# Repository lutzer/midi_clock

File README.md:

# Midi Clock

## Requirements

* install rust
  * run `curl --proto '=https' --tlsv1.2 -sSf https://sh.rustup.rs | sh` to install rust toolchain
  * use nightly toolchain: `rustup default nightly` (for heap allocator)
  * install target `rustup target install thumbv7m-none-eabi`
  * install cargo-edit `cargo install cargo-edit`, it allows to add dependencies with `cargo add <package>`

* install flash toolchain
  * install stlink on mac with `brew install stlink`
  * install *binutils-arm-none-eabi* with `brew tap PX4/homebrew-px4; brew install gcc-arm-none-eabi`

## Connect Board

* disconnect external power supply
* connect programmer *ST-Link V2* to programming pins of blue pill. Connect pins *SWDIO, GND, SWCLK, and 3.3V and RST to pin R*
* check if programmer is avalaible with `st-info --probe`

## Flash Chip

* run `./flash`
* compile with features with `./flash "feature1,feature2,..."`

## Debugging

* for debugging connect serial adapter, see in [docs/hardware.md](docs/hardware.md)
* flash chip with debug feature: `./flash debug`
* see debugging output with `screen /dev/tty.<adapter> 115200`, (Ctrl+A, K to close monitor)
* for analyzing the timings of the midi clock see [tools/clock_test/README.md](tools/clock_test/README.md)

## Links

* Midi specifications: https://www.midi.org/specifications-old/item/table-1-summary-of-midi-message
* STM32f103 Reference Manual: https://www.st.com//content/ccc/resource/technical/document/reference_manual/59/b9/ba/7f/11/af/43/d5/CD00171190.pdf/files/CD00171190.pdf/jcr:content/translations/en.CD00171190.pdf
* LCD 0802A: http://www.farnell.com/datasheets/50552.pdf
* Timer registers for stm32f103: https://docs.rs/stm32f1/0.14.0/stm32f1/stm32f103/tim2/index.html

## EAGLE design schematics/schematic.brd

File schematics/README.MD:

# Midi Clock Schematics

## Setup
* copy libraries from libraries folder to eagle libraries folder
* copy schematics to eagle project folder
* open project
* activate libraries with right click and use in library manager -> use library

## BOM

## PCB Specs

* drill whole sice 0.2mm - 6.3mm
* via size: hole: 0.2mm, copper ring: 0.4mm
* plated hole size: 0.2-6.35
* min clearences
  * hole to hole: 0.5mm
  * via to via: 0.254mm
  * pad to pad with hole: 0.5mm
  * pth to track: 0.33
  * pad to track: 0.2
  * trace width: minimum 0.2mm
  * spacing: 0.2mm

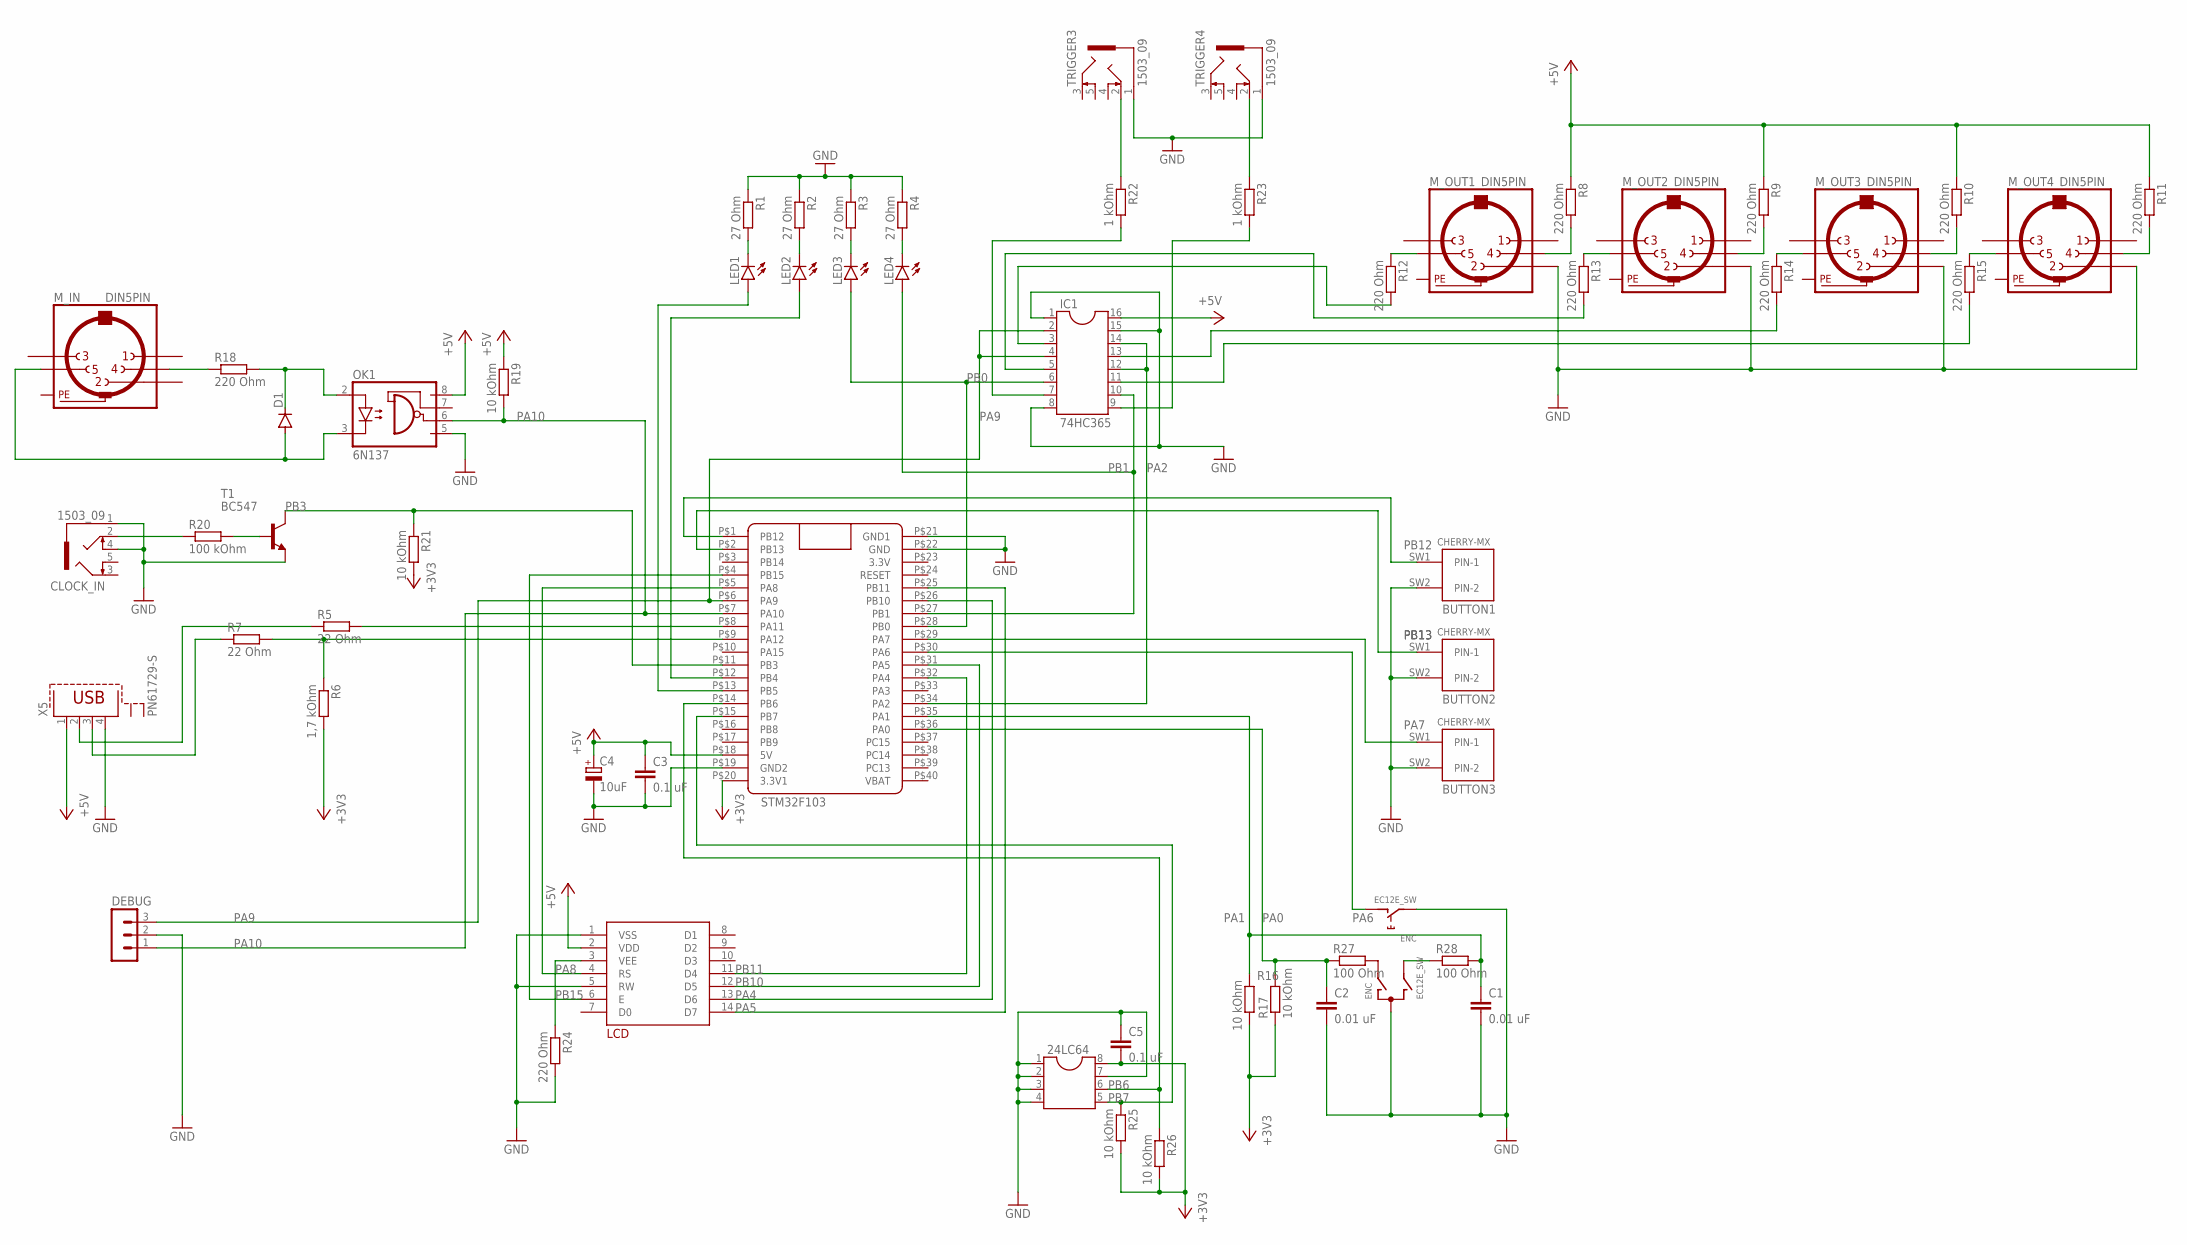
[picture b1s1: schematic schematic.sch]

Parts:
24LC64: DIL8; DIL08
BUTTON1, BUTTON2, BUTTON3: CHERRY-MX
C1, C2: 0.01 uF; C050-025X075
C3, C5: 0.1 uF; C050-025X075
C4: 10uF; E2,5-6
CLOCK_IN: 1503_09
D1: 1N4446; DO35-10
DEBUG: MA03-1
ENC: EC12E_SW; ALPS_EC12E_SW
IC1: 74HC365; SOCKET-16
LCD: LCD-MODUL2X8
LED1, LED2, LED3, LED4: LED3MM
M_IN: DIN5PIN; MABPM5S
M_OUT1, M_OUT2, M_OUT3, M_OUT4: DIN5PIN; MABPM5S
OK1: 6N137; DIL08
R1, R2, R3, R4: 27 Ohm; 0207/10
R5, R7: 22 Ohm; 0207/10
R6: 1,7 kOhm; 0207/10
R8, R9, R10, R11, R12, R13, R14, R15, R18, R24: 220 Ohm; 0207/10
R16, R17, R19, R21, R25, R26: 10 kOhm; 0207/10
R20: 100 kOhm; 0207/10
R22, R23: 1 kOhm; 0207/10
R27, R28: 100 Ohm; 0207/10
STM32F103: BLUE_PILL
T1: BC547; TO92
TRIGGER3, TRIGGER4: 1503_09
X5: PN61729-S

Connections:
+3V3: 24LC64.8, C5.2, R6.2, R16.2, R17.1, R21.2, R25.2, R26.2, STM32F103.P$20 (3.3V1)
+5V: C3.1, C4.+, IC1.16, LCD.2 (VDD), OK1.8 (VCC), R8.1, R9.1, R10.1, R11.1, R19.1, STM32F103.P$18 (5V), X5.1
GND: 24LC64.1, 24LC64.2, 24LC64.3, 24LC64.4, 24LC64.7, BUTTON1.SW2 (PIN-2), BUTTON2.SW2 (PIN-2), BUTTON3.SW2 (PIN-2), C1.2, C2.2, C3.2, C4.-, C5.1, CLOCK_IN.1, CLOCK_IN.4, DEBUG.2, ENC.C, ENC.E (2), IC1.1, IC1.8, IC1.15, LCD.1 (VSS), LCD.5 (RW), M_OUT1.P2 (2), M_OUT2.P2 (2), M_OUT3.P2 (2), M_OUT4.P2 (2), OK1.5 (GND), R1.1, R2.1, R3.1, R4.1, R24.2, STM32F103.P$19 (GND2), STM32F103.P$21 (GND1), STM32F103.P$22 (GND), T1.1 (E), TRIGGER3.1, TRIGGER4.1, X5.4
unnamed: R5.1, X5.2
unnamed: R5.2, STM32F103.P$8 (PA11)
unnamed: R7.1, X5.3
unnamed: LED1.K (C), R1.2
unnamed: LED2.K (C), R2.2
unnamed: LED3.K (C), R3.2
unnamed: LED4.K (C), R4.2
unnamed: R6.1, R7.2, STM32F103.P$9 (PA12)
unnamed: M_OUT1.P4 (4), R8.2
unnamed: M_OUT2.P4 (4), R9.2
unnamed: M_OUT3.P4 (4), R10.2
unnamed: M_OUT4.P4 (4), R11.2
unnamed: M_OUT1.P5 (5), R12.1
unnamed: M_OUT2.P5 (5), R13.1
unnamed: M_OUT3.P5 (5), R14.1
unnamed: M_OUT4.P5 (5), R15.1
unnamed: IC1.3, R12.2
unnamed: IC1.5, R13.2
unnamed: IC1.13, R14.2
unnamed: IC1.11, R15.2
unnamed: ENC.A, R27.2
unnamed: ENC.B, R28.1
unnamed: D1.C, OK1.2 (A), R18.2
unnamed: D1.A, M_IN.P5 (5), OK1.3 (C)
unnamed: M_IN.P4 (4), R18.1
unnamed: LCD.3 (VEE), R24.1
unnamed: CLOCK_IN.2, R20.1
unnamed: R20.2, T1.2 (B)
unnamed: R22.1, TRIGGER3.2
unnamed: IC1.7, R22.2
unnamed: R23.1, TRIGGER4.2
unnamed: IC1.9, R23.2
PA0: C2.1, R17.2, R27.1, STM32F103.P$36 (PA0)
PA1: C1.1, R16.1, R28.2, STM32F103.P$35 (PA1)
PA2: IC1.12, IC1.14, STM32F103.P$34 (PA2)
PA4: LCD.11 (D4), STM32F103.P$32 (PA4)
PA5: LCD.12 (D5), STM32F103.P$31 (PA5)
PA6: ENC.D (1), STM32F103.P$30 (PA6)
PA7: BUTTON3.SW1 (PIN-1), STM32F103.P$29 (PA7)
PA8: LCD.4 (RS), STM32F103.P$5 (PA8)
PA9: DEBUG.3, IC1.2, IC1.4, STM32F103.P$6 (PA9)
PA10: DEBUG.1, OK1.6 (VO), R19.2, STM32F103.P$7 (PA10)
PB0: IC1.6, LED3.A, STM32F103.P$28 (PB0)
PB1: IC1.10, LED4.A, STM32F103.P$27 (PB1)
PB3: R21.1, STM32F103.P$11 (PB3), T1.3 (C)
PB4: LED2.A, STM32F103.P$12 (PB4)
PB5: LED1.A, STM32F103.P$13 (PB5)
PB6: 24LC64.6, R26.1, STM32F103.P$14 (PB6)
PB7: 24LC64.5, R25.1, STM32F103.P$15 (PB7)
PB10: LCD.13 (D6), STM32F103.P$26 (PB10)
PB11: LCD.14 (D7), STM32F103.P$25 (PB11)
PB12: BUTTON1.SW1 (PIN-1), STM32F103.P$1 (PB12)
PB13: BUTTON2.SW1 (PIN-1), STM32F103.P$2 (PB13)
PB15: LCD.6 (E), STM32F103.P$4 (PB15)
PE: M_IN.PE, M_IN.PE@ (PE), M_OUT1.PE, M_OUT1.PE@ (PE), M_OUT2.PE, M_OUT2.PE@ (PE), M_OUT3.PE, M_OUT3.PE@ (PE), M_OUT4.PE, M_OUT4.PE@ (PE)

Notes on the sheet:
STM32F103

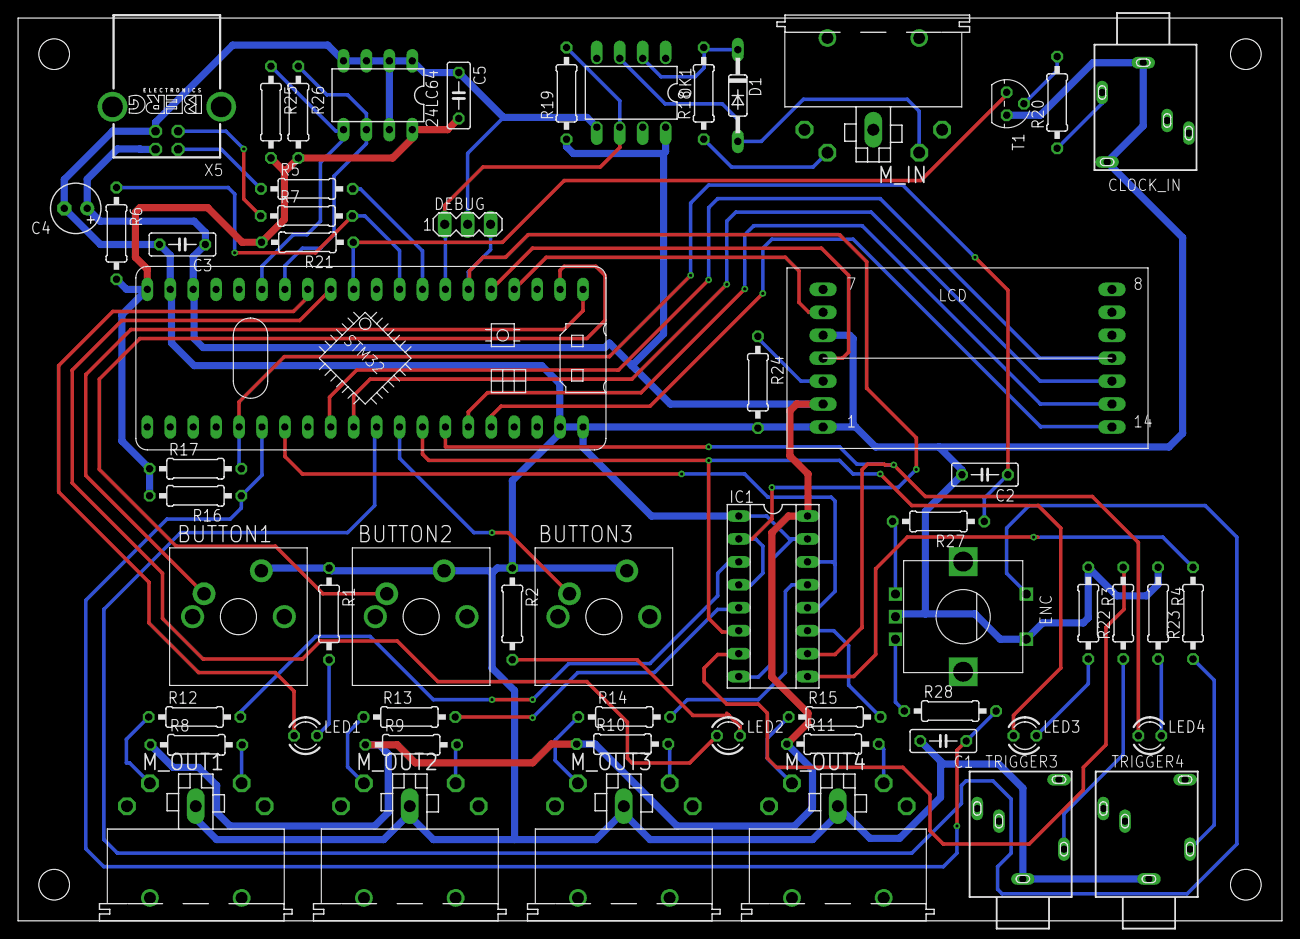
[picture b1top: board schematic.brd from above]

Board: 2 copper layers, 140.0 x 100.0 mm, 58 parts (0 on the bottom side), 58 nets.

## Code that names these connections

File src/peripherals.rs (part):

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use embedded_hal::digital::v2::{OutputPin, InputPin};

// types for Initialized peripherals
pub type Trigger1Gpio = gpio::gpiob::PB5<gpio::Output<gpio::PushPull>>;
pub type Trigger2Gpio = gpio::gpiob::PB4<gpio::Output<gpio::PushPull>>;
pub type Trigger3Gpio = gpio::gpiob::PB0<gpio::Output<gpio::PushPull>>;
pub type Trigger4Gpio = gpio::gpiob::PB1<gpio::Output<gpio::PushPull>>;

pub type Button1Gpio = gpio::gpiob::PB12<gpio::Input<gpio::PullUp>>;
pub type Button2Gpio = gpio::gpiob::PB13<gpio::Input<gpio::PullUp>>;
pub type Button3Gpio = gpio::gpioa::PA7<gpio::Input<gpio::PullUp>>;
pub type Button4Gpio = gpio::gpioa::PA6<gpio::Input<gpio::PullUp>>;

pub struct DisplayPins {
  pub rs: gpio::gpioa::PA8<gpio::Output<gpio::PushPull>>,
  pub en: gpio::gpiob::PB15<gpio::Output<gpio::PushPull>>,
  pub d4: gpio::gpiob::PB11<gpio::Output<gpio::PushPull>>,
  pub d5: gpio::gpiob::PB10<gpio::Output<gpio::PushPull>>,
  pub d6: gpio::gpioa::PA4<gpio::Output<gpio::PushPull>>,
  pub d7: gpio::gpioa::PA5<gpio::Output<gpio::PushPull>>
}

pub type I2c1Port = BlockingI2c<pac::I2C1, (
  gpio::gpiob::PB6<gpio::Alternate<gpio::OpenDrain>>,
  gpio::gpiob::PB7<gpio::Alternate<gpio::OpenDrain>>)>;


pub type Usart1Serial = Serial<
  USART1, (gpio::gpioa::PA9<gpio::Alternate<gpio::PushPull>>, 
  gpio::gpioa::PA10<gpio::Input<gpio::Floating>>)>;

pub type Usart2Serial = Serial<
    USART2, (gpio::gpioa::PA2<gpio::Alternate<gpio::PushPull>>, 
    gpio::gpioa::PA3<gpio::Input<gpio::Floating>>)>;

// holds all peripherals
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    let mut gpioc = dp.GPIOC.split(&mut apb2);
    let mut afio = dp.AFIO.constrain(&mut apb2);

    // disable jtag debugging on pa15,pb3,pb4
    let (_, _, gpiob_pb4) = afio.mapr.disable_jtag(gpioa.pa15, gpiob.pb3, gpiob.pb4);

    // init timers
    Timer2::init(dp.TIM2, &clocks, &mut apb1);
    Timer3::init(dp.TIM3, &clocks, &mut apb1);

    // init encoder interrupts
    Encoder::init(&dp.EXTI, gpioa.pa0, gpioa.pa1, &mut gpioa.crl, &mut afio );

    // setup delay
    let delay = Delay::new(cp.SYST, clocks);

    return Peripherals {
      trigger1: Peripherals::init_trigger1(gpiob.pb5, &mut gpiob.crl),
      trigger2: Peripherals::init_trigger2(gpiob_pb4, &mut gpiob.crl),
      trigger3: Peripherals::init_trigger3(gpiob.pb0, &mut gpiob.crl),
      trigger4: Peripherals::init_trigger4(gpiob.pb1, &mut gpiob.crl),

      button1: Peripherals::init_button1(gpiob.pb12, &mut gpiob.crh),
      button2: Peripherals::init_button2(gpiob.pb13, &mut gpiob.crh),
      button3: Peripherals::init_button3(gpioa.pa7, &mut gpioa.crl),
      button4: Peripherals::init_button4(gpioa.pa6, &mut gpioa.crl),

      usart1: Peripherals::init_usart1(dp.USART1, gpioa.pa9, gpioa.pa10, &mut gpioa.crh, &mut afio, &clocks, &mut apb2),
      usart2: Peripherals::init_usart2(dp.USART2, gpioa.pa2, gpioa.pa3, &mut gpioa.crl, &mut afio, &clocks, &mut apb1),
      
      display: Peripherals::init_display(gpioa.pa8, gpiob.pb15, gpiob.pb11, gpiob.pb10, 
        gpioa.pa4, gpioa.pa5, &mut gpiob.crh, &mut gpioa.crh, &mut gpioa.crl),

      i2c1: Peripherals::init_i2c1(dp.I2C1, gpiob.pb6, gpiob.pb7, &mut gpiob.crl, 
        &mut afio, &clocks, &mut apb1),

      delay: Some(delay)
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  }

  fn init_trigger1(
    pb5: gpio::gpiob::PB5<gpio::Input<gpio::Floating>>, 
    crl: &mut gpio::gpiob::CRL
  ) -> Option<Trigger1Gpio> {
    let mut trigger = pb5.into_push_pull_output(crl);
    trigger.set_low().ok();
    return Some(trigger);
  }

  fn init_trigger2(
    pb4: gpio::gpiob::PB4<gpio::Input<gpio::Floating>>, 
    crl: &mut gpio::gpiob::CRL
  ) -> Option<Trigger2Gpio> {
    let mut trigger = pb4.into_push_pull_output(crl);
    trigger.set_low().ok();
    return Some(trigger);
  }

  fn init_trigger3(
    pb0: gpio::gpiob::PB0<gpio::Input<gpio::Floating>>, 
    crl: &mut gpio::gpiob::CRL
  ) -> Option<Trigger3Gpio> {
    let mut trigger = pb0.into_push_pull_output(crl);
    trigger.set_low().ok();
    return Some(trigger);
  }

  fn init_trigger4(
    pb1: gpio::gpiob::PB1<gpio::Input<gpio::Floating>>, 
    crl: &mut gpio::gpiob::CRL
  ) -> Option<Trigger4Gpio> {
    let mut trigger = pb1.into_push_pull_output(crl);
    trigger.set_low().ok();
    return Some(trigger);
  }

  fn init_button1(
    pb12: gpio::gpiob::PB12<gpio::Input<gpio::Floating>>, 
    crh: &mut gpio::gpiob::CRH
  ) -> Option<Button1Gpio> {
    let button = pb12.into_pull_up_input(crh);
    return Some(button);
  }

  fn init_button2(
    pb13: gpio::gpiob::PB13<gpio::Input<gpio::Floating>>, 
    crh: &mut gpio::gpiob::CRH
  ) -> Option<Button2Gpio> {
    let button = pb13.into_pull_up_input(crh);
    return Some(button);
  }

  fn init_button3(
    pa7: gpio::gpioa::PA7<gpio::Input<gpio::Floating>>, 
    crl: &mut gpio::gpioa::CRL
  ) -> Option<Button3Gpio> {
    let button = pa7.into_pull_up_input(crl);
    return Some(button);
  }

  fn init_button4(
    pa6: gpio::gpioa::PA6<gpio::Input<gpio::Floating>>, 
    crl: &mut gpio::gpioa::CRL
  ) -> Option<Button4Gpio> {
    let button = pa6.into_pull_up_input(crl);
    return Some(button);
  }

  fn init_usart1(
    usart1: USART1, 
    pa9: gpio::gpioa::PA9<gpio::Input<gpio::Floating>>,
    pa10: gpio::gpioa::PA10<gpio::Input<gpio::Floating>>,
    crh: &mut gpio::gpioa::CRH,
    afio: &mut afio::Parts, 
    clocks: &stm32f1xx_hal::rcc::Clocks, 
    apb2: &mut stm32f1xx_hal::rcc::APB2
  ) -> Option<Usart1Serial> {
    let tx = pa9.into_alternate_push_pull(crh);
    let rx = pa10;

    let serial = Serial::usart1(
      usart1,
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
  fn init_usart2(
    usart2: USART2, 
    pa2: gpio::gpioa::PA2<gpio::Input<gpio::Floating>>,
    pa3: gpio::gpioa::PA3<gpio::Input<gpio::Floating>>,
    crl: &mut gpio::gpioa::CRL,
    afio: &mut afio::Parts, 
    clocks: &stm32f1xx_hal::rcc::Clocks, 
    apb1: &mut stm32f1xx_hal::rcc::APB1
  ) -> Option<Usart2Serial> {
    let tx = pa2.into_alternate_push_pull(crl);
    let rx = pa3;

    let serial = Serial::usart2(
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  }

  fn init_display(
    pa8: gpio::gpioa::PA8<gpio::Input<gpio::Floating>>,
    pb15: gpio::gpiob::PB15<gpio::Input<gpio::Floating>>,
    pb11: gpio::gpiob::PB11<gpio::Input<gpio::Floating>>,
    pb10: gpio::gpiob::PB10<gpio::Input<gpio::Floating>>,
    pa4: gpio::gpioa::PA4<gpio::Input<gpio::Floating>>,
    pa5: gpio::gpioa::PA5<gpio::Input<gpio::Floating>>,
    crhb: &mut gpio::gpiob::CRH,
    crha: &mut gpio::gpioa::CRH,
    crla: &mut gpio::gpioa::CRL
  ) -> Option<DisplayPins> {

    let display: DisplayPins = DisplayPins{
      rs: pa8.into_push_pull_output(crha),
      en: pb15.into_push_pull_output(crhb),
      d4: pb11.into_push_pull_output(crhb),
      d5: pb10.into_push_pull_output(crhb),
      d6: pa4.into_push_pull_output(crla),
      d7: pa5.into_push_pull_output(crla)
    };

    return Some(display);
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
  fn init_i2c1(
    i2c: pac::I2C1,
    pb6: gpio::gpiob::PB6<gpio::Input<gpio::Floating>>,
    pb7: gpio::gpiob::PB7<gpio::Input<gpio::Floating>>,
    crl: &mut gpio::gpiob::CRL,
    afio: &mut afio::Parts,
    clocks: &stm32f1xx_hal::rcc::Clocks,
    apb1: &mut stm32f1xx_hal::rcc::APB1
  ) -> Option<I2c1Port> {
    // init i2c
    let scl = pb6.into_alternate_open_drain(crl);
    let sda = pb7.into_alternate_open_drain(crl);

    let i2c = BlockingI2c::i2c1(
      i2c,
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
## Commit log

2021-07-24 added blink sketch
2021-07-24 added flash script
2021-07-25 added first working serial interface
2021-07-26 created basic peripherals struct
2021-07-27 added initial peripheral initialisation
2021-07-29 added serial writer"
2021-07-29 fixed imports
2021-07-30 added dynamic allocator
2021-07-30 correction in flash script
2021-08-26 added initial button struct
2021-08-27 added timer handler struct
2021-08-30 added timer2 handlers
2021-09-01 timer is working now, added debug class
2021-09-02 fixed timer2 struct
2021-09-05 added button handler
2021-09-15 added 3 button debounce
2021-09-16 added interrupt detection for encoder
2021-09-16 added encoder interrupt handler
2021-09-16 refactored debugging functions
2021-09-17 added initial version of state machine
2021-09-17 changed handler structure
2021-09-17 refactored change handlers;
2021-09-18 added static context with triggers instance
2021-09-19 added mutex for context
2021-09-19 triggers pulse now at 20ms
2021-09-19 added initial display implementation
2021-09-27 changed clock timer
2021-09-27 fixed encoder interrupts
2021-09-29 refactoring
2021-09-29 added sequence reset
2021-09-29 raised clock frequency
2021-10-01 refactored some timer functions, cleaned up debugging methods
2021-10-03 removed jitter from timer
2021-10-04 added additinal jitter tests
2021-10-06 swapped timer2 with timer3
2021-10-07 added clock analyzer
2021-10-19 updated flash script
2021-10-20 changed clock timer to use overflow counter
2021-10-21 added 4 additional triggers
2021-10-21 added 4 clock outputs
2021-10-22 added trigger multiplier
2021-10-22 changed trigger layout;
2021-10-22 added debug method for state
2021-10-23 added spi display
2021-10-23 cleaned up peripherals
2021-10-24 optimized clock atomic vars
2021-10-25 cleaned up clock settings
2021-10-27 added schematic
2021-10-27 added eeprom chip to schematic
2021-10-28 added lcd8x2 display
2021-10-28 cleaned up libs
2021-11-05 lcd is now working
2021-11-05 added addiotional commands
2021-11-05 updated timings
2021-11-06 added basic eeprom implementation
2021-11-06 added page write to eeprom;
2021-11-07 better error handling
2021-11-07 tested serial input
2021-11-07 did some cleanup
2021-11-07 updated schematic
2021-11-07 added footprints, started brd
2021-11-07 removed lib files
2021-11-08 finished first version of schematic;
2021-11-09 fixed circuit errors
2021-11-09 fixed some schematic errors
2021-11-09 final pcb design v1.0
